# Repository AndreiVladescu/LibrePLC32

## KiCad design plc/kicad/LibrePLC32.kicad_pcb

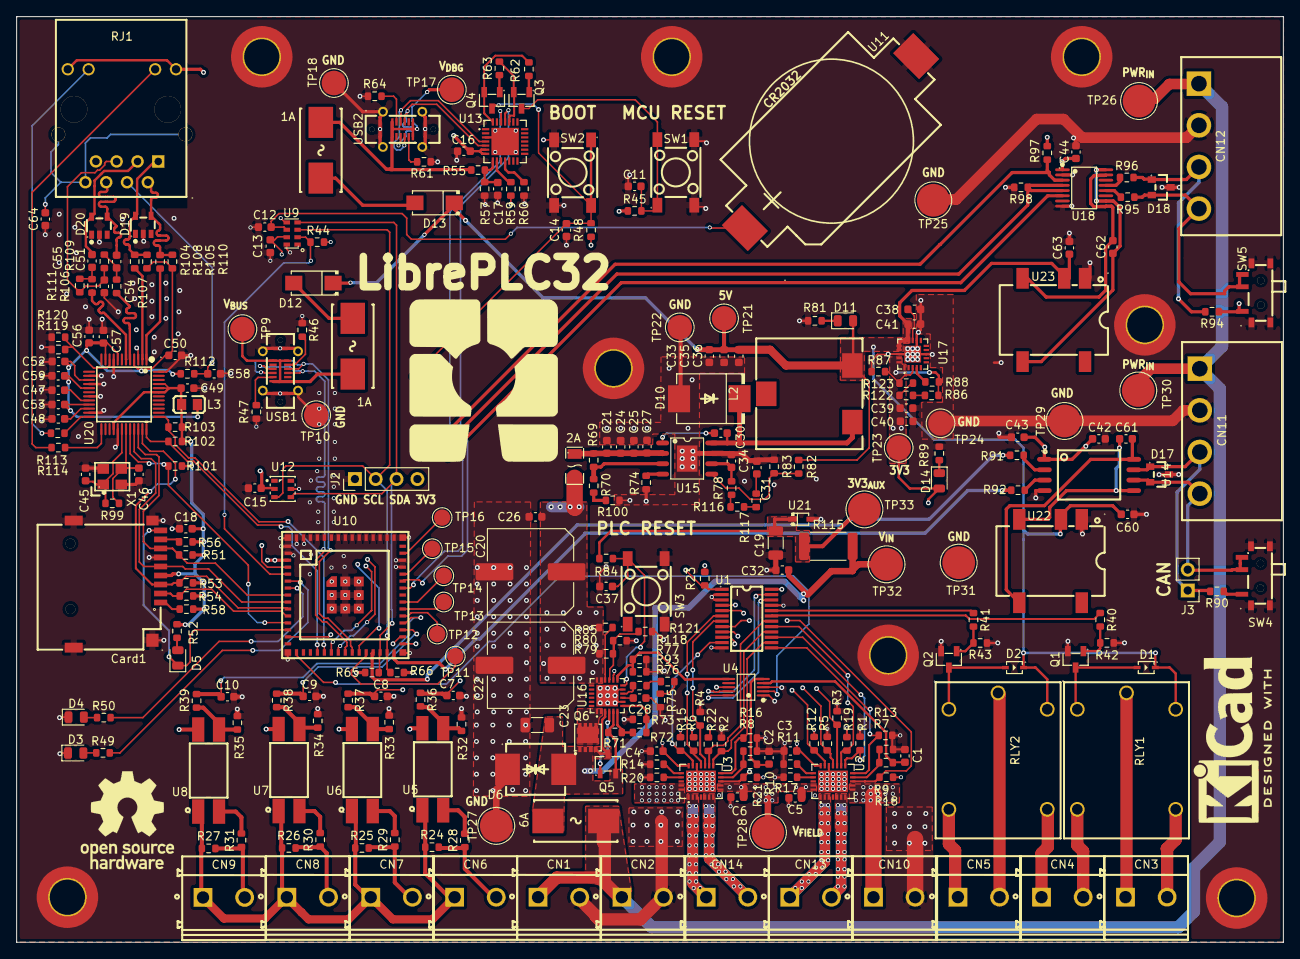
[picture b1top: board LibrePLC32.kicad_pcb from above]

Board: 4 copper layers, 154.5 x 112.9 mm, 292 parts (0 on the bottom side), 185 nets.

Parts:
C1, C2: 100p; C_0603_1608Metric
C3, C4, C21, C24, C25, C27: 2.2u; C_0603_1608Metric
C5, C6, C11, C12, C13, C14, C15, C18, C26, C28, C30, C32, C37, C39, C42, C44, C49, C50, C52, C53, C56, C57, C59: 100n; C_0603_1608Metric
C7, C8, C9, C10, C64: 1n; C_0603_1608Metric
C16, C38, C61, C62: 10u; C_0603_1608Metric
C17, C43: 1u; C_0603_1608Metric
C19, C23: 2.2u; C_1206_3216Metric
C20, C22: 220u; C_Elec_10x10.2
C31: 4.7n; C_0603_1608Metric
C33, C35, C36: 47u; C_0603_1608Metric
C34: 47p; C_0603_1608Metric
C40, C41: 22u; C_0603_1608Metric
C45, C46: 27p; C_0603_1608Metric
C47, C60, C63: 4.7u; C_0603_1608Metric
C48, C54: 10n; C_0603_1608Metric
C51, C55: 6.8n; C_0603_1608Metric
C58: 22n; C_0603_1608Metric
CN1, CN2, CN3, CN4, CN5, CN6, CN7, CN8, CN9, CN10, CN13, CN14: DB128V-5.08-2P-GN-S; CONN-TH_2P-P5.08_DIBO_DB128V-5.08
CN11, CN12: DB2ERC-5.08-4P; CONN-TH_4P-P5.08_DB2ERC-5.08-4P
Card1: TF PUSH; TF-SMD_TF-PUSH
D1, D2: 1N4148WS; SOD-323_L1.8-W1.3-LS2.7-RD
D3, D4, D5, D11, D14: LED; LED_0805_2012Metric
D6: SMCJ36CA; SMC_L6.9-W5.9-LS7.9-BI
D10: B560C; SMC_L6.9-W5.9-LS7.9-RD
D12, D13: SS34; SMA_L4.3-W2.7-LS5.1-RD
D17: SM24CANA-02HTG; SOT-23_L2.9-W1.3-P1.90-LS2.4-BR
D18: CDSOT23-SM712; SOT-23_L2.9-W1.3-P1.90-LS2.4-BR
D19, D20: TS3314PLX; SOT-23-5_L2.9-W1.6-P0.95-LS2.8-BR
F2: BSMD1206C-1200T; F1206
FH1, FH2, FH3: 01550900M; FUSE-SMD_L9.8-W5.0_01550900M
H1, H2, H3, H4, H5, H6, H7, H8: MountingHole_Pad; MountingHole_4.3mm_M4_DIN965_Pad_TopBottom
J2: Conn_01x04_Pin; PinHeader_1x04_P2.54mm_Vertical
J3: Conn_01x02_Pin; PinHeader_1x02_P2.54mm_Vertical
L2: 7.2u; IND-SMD_3P-L13.5-W13.0-P6.9
L3: BLM21PG300SN1D; L0805
Q1, Q2: AO3400A; SOT-23-3_L2.9-W1.3-P1.90-LS2.4-BR
Q3, Q4: L8050QLT1G; SOT-23-3_L2.9-W1.3-P1.90-LS2.4-BR
Q5: BSS138LT1G; SOT-23-3_L2.9-W1.6-P1.90-LS2.8-BR
Q6: CSD19537Q3; DFN-8_L3.3-W3.3-P0.65-BL-3
R1, R2, R3, R4, R5, R6, R13, R16, R19, R22, R42, R43, R69, R79, R85, R88: 100k; R_0603_1608Metric
R7, R8, R117: 620; R_0603_1608Metric
R9, R10, R12, R15, R18, R21, R23, R32, R33, R34, R35, R45, R48, R51, R53, R54, R56, R57, R58, R60, R62, R63, R70, R78, R80, R83, R84, R86, R97, R98, R100, R101, R102, R103, R121: 10k; R_0603_1608Metric
R11, R14, R17, R20, R44, R46, R47, R55, R61, R64, R65, R66, R87, R122: 5.1k; R_0603_1608Metric
R24, R25, R26, R27, R28, R29, R30, R31, R77, R116, R118, R119, R120: 6.2k; R_0603_1608Metric
R36, R37, R38, R39, R40, R41, R59, R75, R76, R81, R93, R123: 1k; R_0603_1608Metric
R49, R50, R52, R89, R113, R114: 470; R_0603_1608Metric
R71: 383k; R_0603_1608Metric
R72: 56k; R_0603_1608Metric
R73: 15k; R_0603_1608Metric
R74: 243k; R_0603_1608Metric
R82: 52.5k; R_0603_1608Metric
R90, R94: 120; R_0603_1608Metric
R91, R92: 0; R_0603_1608Metric
R95, R96, R112: 10; R_0603_1608Metric
R99: 1M; R_0603_1608Metric
R104, R105, R106, R107: 33; R_0603_1608Metric
R108, R109, R110, R111: 49; R_0603_1608Metric
R115: 3k; R_2512_6332Metric
RJ1: HR913129A; RJ45-TH_HR913129A
RLY1, RLY2: HF3FF/005-1ZTF; RELAY-TH_HF3FF-018-1ZT
SW1, SW2, SW3: TSD003B08026A03; SW-SMD_4P-L6.0-W6.0-P4.50-LS8.6
SW4, SW5: MSK12C02; SW-TH_MSK12C02
TP9, TP10, TP17, TP18, TP21, TP22, TP23, TP24: TestPoint; TestPoint_Pad_D3.0mm
TP11, TP12, TP13, TP14, TP15, TP16: TestPoint; TestPoint_Pad_D2.0mm
TP25, TP26, TP27, TP28, TP29, TP30, TP31, TP32, TP33: TestPoint; TestPoint_Pad_D4.0mm
U1: TCA9535PWR; TSSOP-24_L7.8-W4.4-P0.65-LS6.4-BL
U2, U3: TPS272C45DRHFR; VQFN-24_L5.0-W4.0-P0.50-BL-EP-1
U4: ADS1115IDGSR; MSOP-10_L3.0-W3.0-P0.50-LS5.0-BL
U5, U6, U7, U8: LTV-814S-TA1-A; OPTO-SMD-4_L4.6-W6.5-P2.54-LS10.3-BL
U9: RV-3028-C7; OSC-SMD_8P-L3.2-W1.5-P0.90-BL
U10: ESP32-S3-MINI-1U; BULETM-SMD_ESPRESSIF_ESP32-S3-MINI-1U-N8
U11: BS-0601-SK-4W; BAT-SMD_BS-06-B4AA012
U12: AHT20; SENSOR-SMD_L3.0-W3.0-P1.00-BR
U13: CP2102N-A02-GQFN28R; QFN-28_L5.0-W5.0-P0.50-TL-EP3.3
U14: ISO1042BDWVR; SOIC-8_L5.9-W7.5-P1.27-LS11.5-BL
U15: TPS54560BDDAR; POWERPAD-SO-8_L4.9-W3.9-P1.27-LS6.0-BL-EP
U16: TPS26630RGER; TQFN-24_L4.0-W4.0-P0.50-TL-EP
U17: TPS7A5201QRGRRQ1; VQFN-20_L3.5-W3.5-P0.50-TL-EP
U18: ISO1500DBQR; SSOP-16_L4.9-W3.9-P0.64-LS6.0-BL
U20: W5500; LQFP-48_L7.0-W7.0-P0.50-LS9.0-BL
U21: BZT52C3V3S; SOD-323_L1.7-W1.3-LS2.5-RD-1
U22, U23: B0505XT-1WR3; PWRM-SMD_BXXXXXT-1WR3
USB1, USB2: GT-USB-7055BB; USB-C-TH_GT-USB-7055BB
X1: X322525MRB4SI; OSC-SMD_4P-L3.2-W2.5-BL_SIT8008BI

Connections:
+3V3: C3.1, C4.1, C13.2, C15.1, C16.2, C18.2, C39.2, C40.2, C42.1, C43.1, C44.1, C49.1, Card1.4 (VDD), D14.2 (A), J2.4, L3.1, R12.1, R15.1, R18.1, R19.1, R21.1, R22.1, R23.1, R44.2, R45.1, R48.1, R51.2, R52.2, R53.2, R54.2, R56.2, R58.2, R59.1, R65.1, R66.1, R86.1, R88.2, R97.1, R101.1, R102.1, R103.1, RJ1.9 (LED(G)_A), RJ1.12 (LED(Y)_A), TP23.1 (1_1), U1.24 (VCC), U2.19 (VDD), U3.19 (VDD), U4.8 (VDD), U5.4, U6.4, U7.4, U8.4, U9.7 (VDD), U10.3 (3V3), U12.2 (VDD), U13.6 (VDD), U13.7 (VREGIN), U14.1 (VCC1), U17.1 (OUT), U17.19 (OUT), U17.20 (OUT), U18.1 (VCC1), U20.28 (VDD), U20.43 (PMODE2), U20.44 (PMODE1), U20.45 (PMODE0)
+3V3A: C50.1, C52.1, C53.1, C56.1, C57.1, C59.1, L3.2, R108.2, R110.2, R112.1, U20.4 (AVDD), U20.8 (AVDD), U20.11 (AVDD), U20.15 (AVDD), U20.17 (AVDD), U20.21 (AVDD)
+3V3_AUX: C19.1, R84.1, R115.1, TP33.1 (1_1), U21.1
+5V: C33.2, C35.2, C36.2, C41.2, C60.1, C63.1, D1.1 (K), D2.1 (K), D11.2 (A), D12.1 (C), D13.1 (C), L2.2, R82.1, RLY1.4, RLY2.4, TP21.1 (1_1), U17.14 (EN), U17.15 (IN), U17.16 (IN), U17.17 (IN), U22.2 (Vin), U23.2 (Vin)
/CAN/CAN_H: CN11.3, D17.1, J3.1, R90.2, U14.7 (CANH)
/CAN/CAN_L: CN11.4, D17.2, J3.2, SW4.2, SW4.3, U14.6 (CANL)
/CAN/CAN_RX: R92.2, U10.30 (IO48)
/CAN/CAN_TX: R91.2, U10.27 (IO47)
/Ethernet/ETH_1V2: C48.1, U20.22 (1V2O)
/Ethernet/ETH_EXPRES: R119.1, R120.1, U20.10 (EXRES1)
/Ethernet/ETH_LED_G: R114.2, U20.25 (LINKLED)
/Ethernet/ETH_LED_Y: R113.2, U20.24 (SPDLED)
/Ethernet/ETH_RX+: R106.1, U20.6 (RXP)
/Ethernet/ETH_RX-: R107.1, U20.5 (RXN)
/Ethernet/ETH_TOCAP: C47.1, U20.20 (TOCAP)
/Ethernet/ETH_TX+: R104.1, U20.2 (TXP)
/Ethernet/ETH_TX-: R105.1, U20.1 (TXN)
/Ethernet/ETH_XI: C45.2, R99.1, U20.30 (XI/CLKIN), X1.1 (OSC1)
/Ethernet/ETH_XO: C46.1, R99.2, U20.31 (XO), X1.3 (OSC2)
/Ethernet/RJ45_RCT: C54.1, R109.1, R111.1, RJ1.5 (RCT)
/Ethernet/RJ45_RX+: C55.2, D20.5, RJ1.3 (RD+)
/Ethernet/RJ45_RX-: C51.2, D20.4, RJ1.6 (RD-)
/Ethernet/RJ45_TCT: C58.1, R112.2, RJ1.4 (TCT)
/Ethernet/RJ45_TX+: D19.5, R104.2, R108.1, RJ1.1 (TD+)
/Ethernet/RJ45_TX-: D19.4, R105.2, R110.1, RJ1.2 (TD-)
/Ethernet/RXN: C51.1, R107.2, R109.2
/Ethernet/RXP: C55.1, R106.2, R111.2
/Ethernet/SPI_MISO: Card1.7 (DAT0), R51.1, U10.8 (IO4), U20.34 (MISO)
/Ethernet/SPI_MOSI: Card1.3 (CMD), R53.1, U10.10 (IO6), U20.35 (MOSI)
/Ethernet/SPI_SCLK: Card1.5 (CLX), U10.9 (IO5), U20.33 (SCLK)
/Ethernet/~ETH_CS: R101.2, U10.12 (IO8), U20.32 (SCSn)
/Ethernet/~ETH_INT: R102.2, U10.19 (IO15), U20.36 (INTn)
/Ethernet/~ETH_RST: R103.2, U10.20 (IO16), U20.37 (RSTn)
/MCU/ADC_RDY: U4.2 (ALERT/RDY), U10.16 (IO12)
/MCU/I2C_SCL: J2.2, R66.2, U1.22 (SCL), U4.10 (SCL), U9.3 (SCL), U10.29 (IO34), U12.3 (SCL)
/MCU/I2C_SDA: J2.3, R65.2, U1.23 (SDA), U4.9 (SDA), U9.4 (SDA), U10.28 (IO33), U12.4 (SDA)
/MCU/MCU_DI1: C7.1, R36.1, U10.31 (IO35)
/MCU/MCU_DI2: C8.1, R37.1, U10.32 (IO36)
/MCU/MCU_DI3: C9.1, R38.1, U10.33 (IO37)
/MCU/MCU_DI4: C10.1, R39.1, U10.34 (IO38)
/MCU/MCU_USB_D+: U10.24 (USB_D+), USB1.A6 (D+), USB1.B6 (D+)
/MCU/MCU_USB_D-: U10.23 (USB_D-), USB1.A7 (D-), USB1.B7 (D-)
/MCU/SD_CD: Card1.CD, D5.1 (K), U10.13 (IO9)
/MCU/SD_DAT1: Card1.8 (DAT1), R56.1
/MCU/SD_DAT2: Card1.1 (DAT2), R58.1
/MCU/S_LED0: R49.2, U10.6 (IO2)
/MCU/S_LED1: R50.2, U10.7 (IO3)
/MCU/UART_DTR: Q4.2 (E), R62.2, U13.28 (DTR)
/MCU/UART_RTS: Q3.2 (E), R63.2, U13.24 (RTS)
/MCU/UART_RX: U10.40 (RXD0), U13.25 (RXD)
/MCU/UART_TX: U10.39 (TXD0), U13.26 (TXD)
/MCU/USB_D+: U13.4 (D+), USB2.A6 (D+), USB2.B6 (D+)
/MCU/USB_D-: U13.5 (D-), USB2.A7 (D-), USB2.B7 (D-)
/MCU/~MCU_BOOT: C14.2, Q4.3 (C), R48.2, SW2.1, SW2.2, U10.4 (IO0)
/MCU/~MCU_RST: C11.2, Q3.3 (C), R45.2, SW1.1, SW1.2
/MCU/~RTC_INT: R44.1, U9.2 (~INT), U10.5 (IO1)
/MCU/~SD_CS: Card1.2 (CD/DAT3), R54.1, U10.11 (IO7)
/Power/FB: R82.2, R83.1, U15.5 (FB)
/Power/MAIN_FB: R87.1, R123.2, U17.3 (FB)
/Power/MAIN_PG: R88.1, U17.4 (PG)
/Power/PPIC_BGATE: Q5.3 (D), Q6.4 (G), U16.3 (BGATE)
/Power/PPIC_DRV: Q5.1 (G), U16.4 (DRV)
/Power/PPIC_ILIM: R93.1, U16.10 (ILIM)
/Power/PPIC_IMON: R77.1, R118.1, U4.6 (AIN2), U16.13 (IMON)
/Power/PPIC_IN: Q6.5 (D), Q6.6 (D), Q6.7 (D), Q6.8 (D), Q6.9 (D), U16.1 (IN), U16.2 (IN)
/Power/PPIC_OVP: R72.2, R73.1, U16.7 (OVP)
/Power/PPIC_PGOOD: R85.2, U16.16 (PGOOD)
/Power/PPIC_PGTH: R79.2, R80.1, R121.1, U16.15 (PGTH)
/Power/PPIC_UVLO: R71.2, R72.1, U16.6 (UVLO)
/Power/PPIC_dVdT: C28.2, U16.9 (dVdT)
/Power/V_IN_MAIN: C23.2, C32.2, D6.2, FH1.2, Q5.2 (S), Q6.1 (S), Q6.2 (S), Q6.3 (S), R71.1, R115.2, TP32.1 (1_1), U16.5 (IN_SYS)
/Power/~PPIC_SHDN: C37.2, R84.2, SW3.2, U16.12 (~SHDN)
/RS-485/EXT_RS485_A: CN12.4, D18.2, R95.1, SW5.2, SW5.3
/RS-485/EXT_RS485_B: CN12.3, D18.1, R94.2, R96.1
/RS-485/RS485_DIR: R98.1, U10.25 (IO21), U18.4 (~RE), U18.5 (DE)
/RS-485/RS485_RXD: R97.2, U10.21 (IO17), U18.3 (R)
/RS-485/RS485_TXD: U10.22 (IO18), U18.6 (D)
/Terminal Blocks Interface/DI1: CN6.2, R24.1, R28.1
/Terminal Blocks Interface/DI2: CN7.2, R25.1, R29.1
/Terminal Blocks Interface/DI3: CN8.2, R26.1, R30.1
/Terminal Blocks Interface/DI4: CN9.2, R27.1, R31.1
/Terminal Blocks Interface/DI_COM: CN6.1, CN7.1, CN8.1, CN9.1, R24.2, R25.2, R26.2, R27.2, U5.1, U6.1, U7.1, U8.1
/Terminal Blocks Interface/MOS_IN1: R40.1, U1.19 (P16)
/Terminal Blocks Interface/MOS_IN2: R41.1, U1.20 (P17)
/Terminal Blocks Interface/REL_DRV1: D1.2 (A), Q1.3 (D), RLY1.1
/Terminal Blocks Interface/REL_DRV2: D2.2 (A), Q2.3 (D), RLY2.1
/Terminal Blocks Interface/RLY1_NC: CN3.2, RLY1.3
/Terminal Blocks Interface/RLY1_NO: CN4.2, RLY1.2
/Terminal Blocks Interface/RLY2_NC: CN4.1, RLY2.3
/Terminal Blocks Interface/RLY2_NO: CN5.1, RLY2.2
/Terminal Blocks Interface/T1_ADC: C1.1, R9.2, U4.4 (AIN0)
/Terminal Blocks Interface/T1_DIA: R13.1, U1.13 (P10), U2.12 (DIA_EN)
/Terminal Blocks Interface/T1_EN1: R5.1, U1.4 (P00), U2.16 (EN1)
/Terminal Blocks Interface/T1_EN2: R3.1, U1.5 (P01), U2.15 (EN2)
/Terminal Blocks Interface/T1_FLT1: R18.2, U1.8 (P04), U2.10 (FLT1)
/Terminal Blocks Interface/T1_FLT2: R12.2, U1.9 (P05), U2.18 (FLT2)
/Terminal Blocks Interface/T1_ILIM1: R17.1, U2.21 (ILIM1)
/Terminal Blocks Interface/T1_ILIM2: R11.1, U2.20 (ILIM2)
/Terminal Blocks Interface/T1_LATCH: R19.2, U1.17 (P14), U2.14 (LATCH)
/Terminal Blocks Interface/T1_OUT1: CN13.1, U2.1 (OUT1), U2.2 (OUT1), U2.3 (OUT1)
/Terminal Blocks Interface/T1_OUT2: CN13.2, U2.5 (OUT2), U2.6 (OUT2), U2.7 (OUT2)
/Terminal Blocks Interface/T1_SEL: R1.1, U1.15 (P12), U2.13 (SEL)
/Terminal Blocks Interface/T1_SNS: R7.1, R9.1, U2.11 (SNS)
/Terminal Blocks Interface/T2_ADC: C2.1, R10.2, U4.5 (AIN1)
/Terminal Blocks Interface/T2_DIA: R16.1, U1.14 (P11), U3.12 (DIA_EN)
/Terminal Blocks Interface/T2_EN1: R6.1, U1.6 (P02), U3.16 (EN1)
/Terminal Blocks Interface/T2_EN2: R4.1, U1.7 (P03), U3.15 (EN2)
/Terminal Blocks Interface/T2_FLT1: R21.2, U1.10 (P06), U3.10 (FLT1)
/Terminal Blocks Interface/T2_FLT2: R15.2, U1.11 (P07), U3.18 (FLT2)
/Terminal Blocks Interface/T2_ILIM1: R20.1, U3.21 (ILIM1)
/Terminal Blocks Interface/T2_ILIM2: R14.1, U3.20 (ILIM2)
/Terminal Blocks Interface/T2_LATCH: R22.2, U1.18 (P15), U3.14 (LATCH)
/Terminal Blocks Interface/T2_OUT1: CN14.1, U3.1 (OUT1), U3.2 (OUT1), U3.3 (OUT1)
/Terminal Blocks Interface/T2_OUT2: CN14.2, U3.5 (OUT2), U3.6 (OUT2), U3.7 (OUT2)
/Terminal Blocks Interface/T2_SEL: R2.1, U1.16 (P13), U3.13 (SEL)
/Terminal Blocks Interface/T2_SNS: R8.1, R10.1, U3.11 (SNS)
/Terminal Blocks Interface/~GPIO_MUX_INT: R23.2, U1.1 (~INT), U10.14 (IO10)
Earth: C64.2, RJ1.8 (CHSGND), RJ1.13 (SHILED), RJ1.14 (SHILED)
GND: C1.2, C2.2, C3.2, C4.2, C5.2, C6.2, C7.2, C8.2, C9.2, C10.2, C11.1, C12.1, C13.1, C14.1, C15.2, C16.1, C17.2, C18.1, C19.2, C20.2, C21.2, C22.2, C23.1, C24.2, C25.2, C26.1, C27.2, C28.1, C31.1, C32.1, C33.1, C34.1, C35.1, C36.1, C37.1, C38.1, C39.1, C40.1, C41.1, C42.2, C43.2, C44.2, C45.1, C46.2, C47.2, C48.2, C49.2, C50.2, C52.2, C53.2, C54.2, C56.2, C57.2, C58.2, C59.2, C60.2, C63.2, C64.1, CN1.2, CN2.2, CN10.2, CN11.2, CN12.2, Card1.6 (VSS), Card1.10, Card1.11, Card1.12, Card1.13, D3.1 (K), D4.1 (K), D6.1, D10.2 (A), D17.3, D18.3, D19.2, D20.2, H1.1 (1_1), H2.1 (1_1), H3.1 (1_1), H4.1 (1_1), H5.1 (1_1), H6.1 (1_1), H7.1 (1_1), H8.1 (1_1), J2.1, Q1.2 (S), Q2.2 (S), R1.2, R2.2, R3.2, R4.2, R5.2, R6.2, R7.2, R8.2, R11.2, R13.2, R14.2, R16.2, R17.2, R20.2, R32.1, R33.1, R34.1, R35.1, R42.1, R43.1, R46.1, R47.2, R57.1, R60.1, R61.1, R64.2, R73.2, R74.2, R75.2, R77.2, R80.2, R81.2, R83.2, R87.2, R89.2, R98.2, R100.2, R118.2, R119.2, R120.2, R121.2, SW1.3, SW1.4, SW2.3, SW2.4, SW3.3, SW3.4, SW4.4, SW5.4, TP10.1 (1_1), TP18.1 (1_1), TP22.1 (1_1), TP24.1 (1_1), TP25.1 (1_1), TP27.1 (1_1), TP29.1 (1_1), TP31.1 (1_1), U1.2 (A1), U1.3 (A2), U1.12 (GND), U1.21 (A0), U2.17 (GND), U2.25 (EP), U3.17 (GND), U3.25 (EP), U4.1 (ADDR), U4.3 (GND), U9.5 (VSS), U9.8 (EVI), U10.1 (GND), U10.2 (GND), U10.42 (GND), U10.43 (GND), U10.46 (GND), U10.47 (GND), U10.48 (GND), U10.49 (GND), U10.50 (GND), U10.51 (GND), U10.52 (GND), U10.53 (GND), U10.54 (GND), U10.55 (GND), U10.56 (GND), U10.57 (GND), U10.58 (GND), U10.59 (GND), U10.60 (GND), U10.61 (GND), U10.62 (GND), U10.63 (GND), U10.64 (GND), U10.65 (GND), U11.2, U12.5 (GND), U13.3 (GND), U13.29 (EP), U14.4 (GND1), U15.7 (GND), U15.9 (EP), U16.8 (GND), U16.11 (MODE), U16.14 (~FLT), U16.25 (EP), U17.8 (GND), U17.12 (BIAS), U17.18 (GND), U17.21 (EP), U18.2 (GND1), U18.8 (GND1), U20.3 (AGND), U20.9 (AGND), U20.14 (AGND), U20.16 (AGND), U20.19 (AGND), U20.23 (RSVD), U20.29 (GND), U20.48 (AGND), U21.2, U22.1 (GND), U23.1 (GND), USB1.17 (EH), USB1.A1 (GND), USB1.A12 (GND), USB1.B1 (GND), USB1.B12 (GND), USB2.17 (EH), USB2.A1 (GND), USB2.A12 (GND), USB2.B1 (GND), USB2.B12 (GND), X1.2 (GND), X1.4 (GND)
ISO_CAN+: C61.1, U14.8 (VCC2), U22.5 (+Vo)
ISO_CAN-: C61.2, U14.5 (GND2), U22.4 (-Vo)
ISO_RS485+: C62.1, U18.10 (VCC2), U18.16 (VCC2), U23.5 (+Vo)
ISO_RS485-: C62.2, U18.9 (GND2), U18.15 (GND2), U23.4 (-Vo)
unnamed: C31.2, R117.2
unnamed: CN3.1, RLY1.5
unnamed: CN5.2, RLY2.5
unnamed: D3.2 (A), R49.1
unnamed: D4.2 (A), R50.1
unnamed: D5.2 (A), R52.1
unnamed: C30.2, D10.1 (K), L2.1, U15.8 (SW)
unnamed: D11.1 (K), R81.1
unnamed: D12.2 (A), FH2.1
unnamed: D13.2 (A), FH3.1
unnamed: D14.1 (K), R89.1
unnamed: Q1.1 (G), R40.2, R42.2
unnamed: Q2.1 (G), R41.2, R43.2
unnamed: Q3.1 (B), R62.1
unnamed: Q4.1 (B), R63.1
unnamed: R28.2, U5.2
unnamed: R29.2, U6.2
unnamed: R30.2, U7.2
unnamed: R31.2, U8.2
unnamed: R32.2, R36.2, U5.3
unnamed: R33.2, R37.2, U6.3
unnamed: R34.2, R38.2, U7.3
unnamed: R35.2, R39.2, U8.3
unnamed: R75.1, R76.2
unnamed: R76.1, R93.2
unnamed: R90.1, SW4.1
unnamed: R94.1, SW5.1
unnamed: R70.2, R100.1
unnamed: R78.2, R116.1
unnamed: R116.2, R117.1
unnamed: R86.2, R122.1
unnamed: R122.2, R123.1
unnamed: R114.1, RJ1.10 (LED(G)_K)
unnamed: R113.1, RJ1.11 (LED(Y)_K)
unnamed: TP11.1 (1_1), U10.26 (IO26)
unnamed: TP12.1 (1_1), U10.35 (IO39)
unnamed: TP13.1 (1_1), U10.36 (IO40)
unnamed: TP14.1 (1_1), U10.37 (IO41)
unnamed: TP15.1 (1_1), U10.41 (IO45)
unnamed: TP16.1 (1_1), U10.44 (IO46)
unnamed: R59.2, U13.9 (RSTb)
unnamed: R60.2, U13.11 (SUSPENDb)
unnamed: C17.1, R55.2, R57.2, U13.8 (VBUS)
unnamed: R92.1, U14.3 (RXD)
unnamed: R91.1, U14.2 (TXD)
unnamed: C30.1, U15.1 (BOOT)
unnamed: C34.2, R78.1, U15.6 (COMP)
unnamed: R69.2, R70.1, U15.3 (EN)
unnamed: R74.1, U15.4 (RT/CLK)
unnamed: C21.1, C24.1, C25.1, C27.1, F2.1, R69.1, U15.2 (VIN)
unnamed: C38.2, U17.13 (NR/SS)
unnamed: R95.2, U18.12 (A)
unnamed: R96.2, U18.13 (B)
unnamed: R47.1, USB1.A5 (CC1)
unnamed: R46.2, USB1.B5 (CC2)
unnamed: R64.1, USB2.A5 (CC1)
unnamed: R61.2, USB2.B5 (CC2)
PWR_CAN: CN1.1, CN2.1, CN11.1, CN12.1, FH1.1, TP26.1 (1_1), TP30.1 (1_1)
VBUS: FH2.2, TP9.1 (1_1), USB1.A4 (VBUS), USB1.A9 (VBUS), USB1.B4 (VBUS), USB1.B9 (VBUS)
VDBG: FH3.2, R55.1, TP17.1 (1_1), USB2.A4 (VBUS), USB2.A9 (VBUS), USB2.B4 (VBUS), USB2.B9 (VBUS)
V_FIELD: C5.1, C6.1, C20.1, C22.1, C26.2, CN10.1, F2.2, R79.1, R85.1, TP28.1 (1_1), U2.8 (VS), U2.9 (VS), U2.23 (VS), U2.24 (VS), U3.8 (VS), U3.9 (VS), U3.23 (VS), U3.24 (VS), U16.17 (OUT), U16.18 (OUT)
Vbat: C12.2, U9.6 (VBACKUP), U11.1

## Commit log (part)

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2026-04-09 Added CERN Open Hardware Licence Version 2
2026-04-09 Added initial design
2026-04-10 Added transistor outputs
2026-04-10 Added gpio multiplexer and relay circuit
2026-04-10 Updated ethernet circuit
2026-04-10 Added RS 485 circuit
2026-04-10 Added CAN circuit
2026-04-10 Added buck converter circuit
2026-04-11 Added netclasses
2026-04-11 Added the power protection IC
2026-04-11 Wired ESP32-S3 preliminarily
2026-04-11 Added CP2102N bridge
2026-04-11 Added 3.3V regulator
2026-04-12 AHT20 sensor added
2026-04-12 Added more testpads
2026-04-12 Added another power connector
2026-04-12 Added RTC IC
2026-04-12 PCB placement
2026-04-17 Revised CAN circuit
2026-04-18 RS485 circuit reviewed
